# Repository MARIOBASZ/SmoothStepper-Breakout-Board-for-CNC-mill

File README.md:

# SmoothStepper Breakout Board for CNC-mill

A KiCAd project for a single sided PCB with isolated I/0, 10A relay for spindle.
For fully isolated I/O including motor control use stepper drivers such as DM420A or DQ542MA.

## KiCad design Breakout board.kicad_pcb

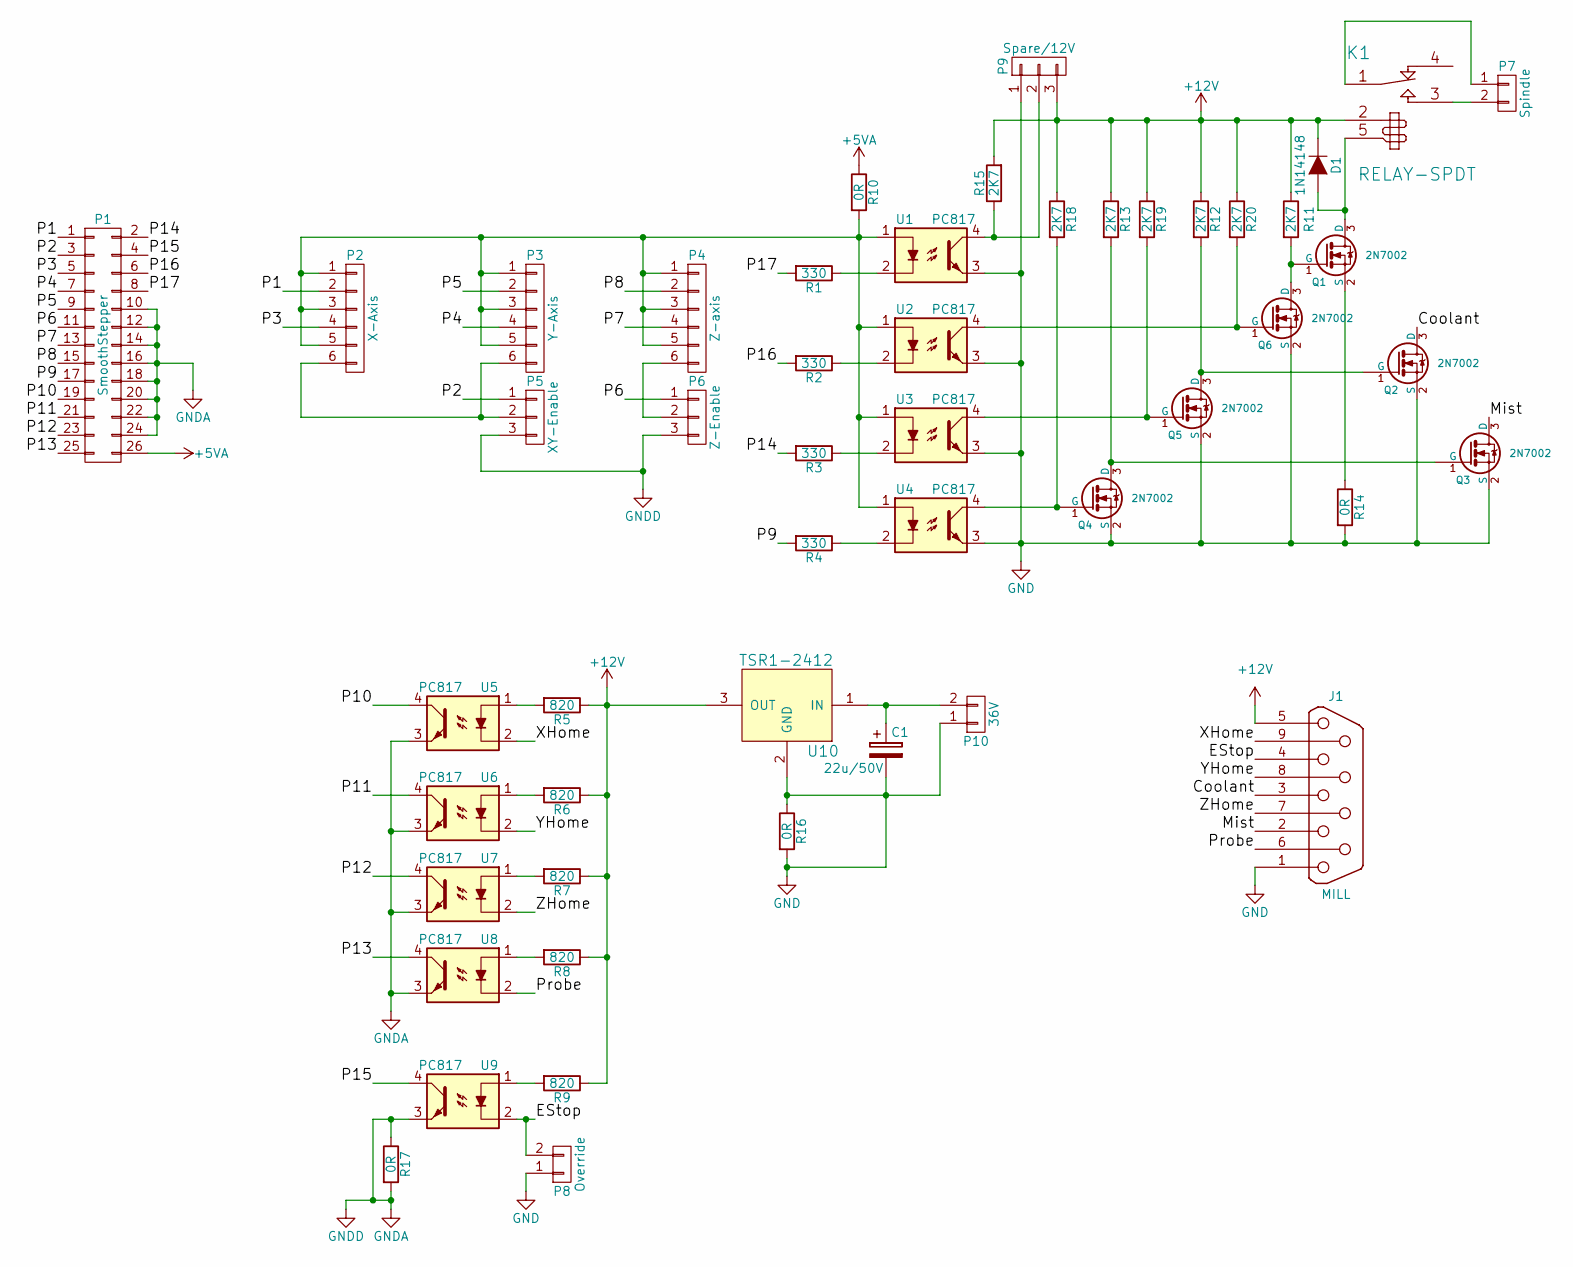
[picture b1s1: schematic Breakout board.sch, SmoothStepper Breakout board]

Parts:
C1: 22u/50V; CP_Tantalum_Case-D_EIA-7343-31_Reflow
D1: 1N14148; D_SOD-123
J1: MILL; DB9_8LCM009S
K1: RELAY-SPDT; Relay_SANYOU_SRD_Series_Form_C
P1: SmoothStepper; IDC_Header_Straight_26pins
P2: X-Axis; CONN_PWR_6P_3.5MM
P3: Y-Axis; CONN_PWR_6P_3.5MM
P4: Z-axis; CONN_PWR_6P_3.5MM
P5: XY-Enable; Pin_Header_Straight_1x03_Pitch2.54mm
P6: Z-Enable; Pin_Header_Straight_1x03_Pitch2.54mm
P7: Spindle; TerminalBlock_Pheonix_MKDS1.5-2pol
P8: Override; Pin_Header_Straight_1x02_Pitch2.54mm
P9: Spare/12V; Pin_Header_Straight_1x03_Pitch2.54mm
P10: 36V; TerminalBlock_Pheonix_MKDS1.5-2pol
Q1, Q2, Q3, Q4, Q5, Q6: 2N7002; SOT-23
R1, R2, R3, R4: 330; R_1206
R5, R6, R7, R8, R9: 820; R_1206
R10, R14, R16, R17: 0R; R_1206
R11, R12, R13, R15, R18, R19, R20: 2K7; R_1206
U1, U2, U3, U4, U5, U6, U7, U8, U9: PC817; OPTOCOUPLER_W00
U10: TSR1-2412; TSR_1

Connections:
+5VA: P1.26, R10.1
/Coolant: J1.3, Q2.3 (D)
/EStop: J1.4, P8.2, U9.2
/Mist: J1.2, Q3.3 (D)
/P1: P1.1, P2.2
/P2: P1.3, P5.1
/P3: P1.5, P2.4
/P4: P1.7, P3.4
/P5: P1.9, P3.2
/P6: P1.11, P6.1
/P7: P1.13, P4.4
/P8: P1.15, P4.2
/P9: P1.17, R4.2
/P10: P1.19, U5.4
/P11: P1.21, U6.4
/P12: P1.23, U7.4
/P13: P1.25, U8.4
/P14: P1.2, R3.2
/P15: P1.4, U9.4
/P16: P1.6, R2.2
/P17: P1.8, R1.2
/Probe: J1.6, U8.2
/XHome: J1.9, U5.2
/YHome: J1.8, U6.2
/ZHome: J1.7, U7.2
GND: C1.2, J1.1, P8.1, P9.1, P10.1, Q2.2 (S), Q3.2 (S), Q4.2 (S), Q5.2 (S), Q6.2 (S), R14.2, R16.1, R16.2, U1.3, U2.3, U3.3, U4.3, U10.2 (GND)
GNDA: P1.10, P1.12, P1.14, P1.16, P1.18, P1.20, P1.22, P1.24, P5.3, P6.3, R17.1, R17.2, U5.3, U6.3, U7.3, U8.3, U9.3
unnamed: C1.1, P10.2, U10.1 (IN)
unnamed: D1.2 (A), K1.5, Q1.3 (D)
unnamed: K1.1 (COM), P7.1
unnamed: K1.3 (NO), P7.2
unnamed: P2.1, P2.3, P2.5, P3.1, P3.3, P3.5, P4.1, P4.3, P4.5, R10.2, U1.1, U2.1, U3.1, U4.1
unnamed: P2.6, P3.6, P5.2
unnamed: P4.6, P6.2
unnamed: Q1.1 (G), Q6.3 (D), R11.2
unnamed: Q1.2 (S), R14.1
unnamed: Q2.1 (G), Q5.3 (D), R12.2
unnamed: Q3.1 (G), Q4.3 (D), R13.2
unnamed: Q4.1 (G), R18.2, U4.4
unnamed: Q5.1 (G), R19.2, U3.4
unnamed: Q6.1 (G), R20.2, U2.4
unnamed: R1.1, U1.2
unnamed: R2.1, U2.2
unnamed: R3.1, U3.2
unnamed: R4.1, U4.2
unnamed: R5.2, U5.1
unnamed: R6.2, U6.1
unnamed: R7.2, U7.1
unnamed: R8.2, U8.1
unnamed: R9.2, U9.1

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
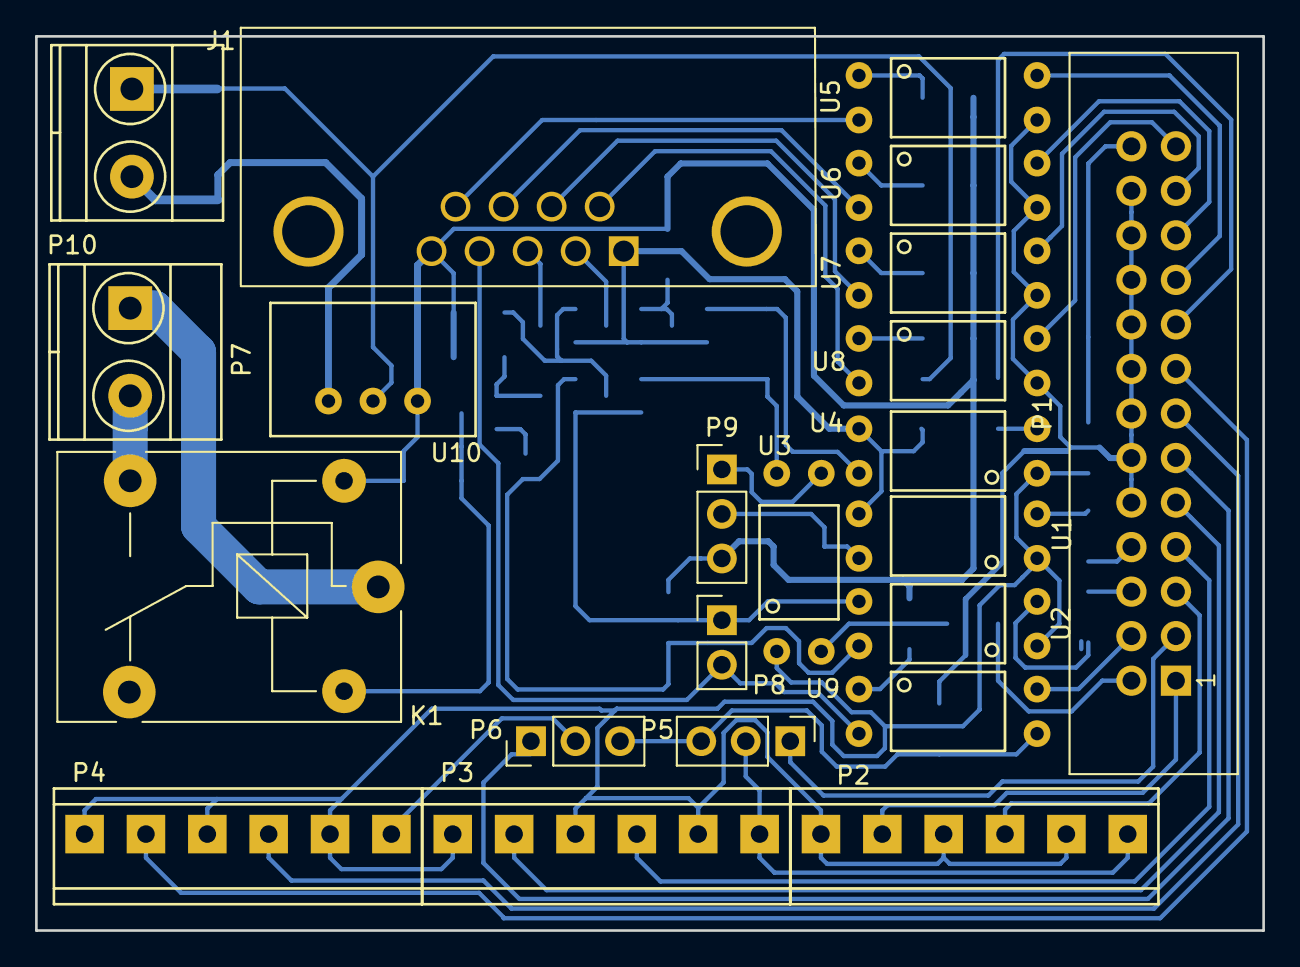
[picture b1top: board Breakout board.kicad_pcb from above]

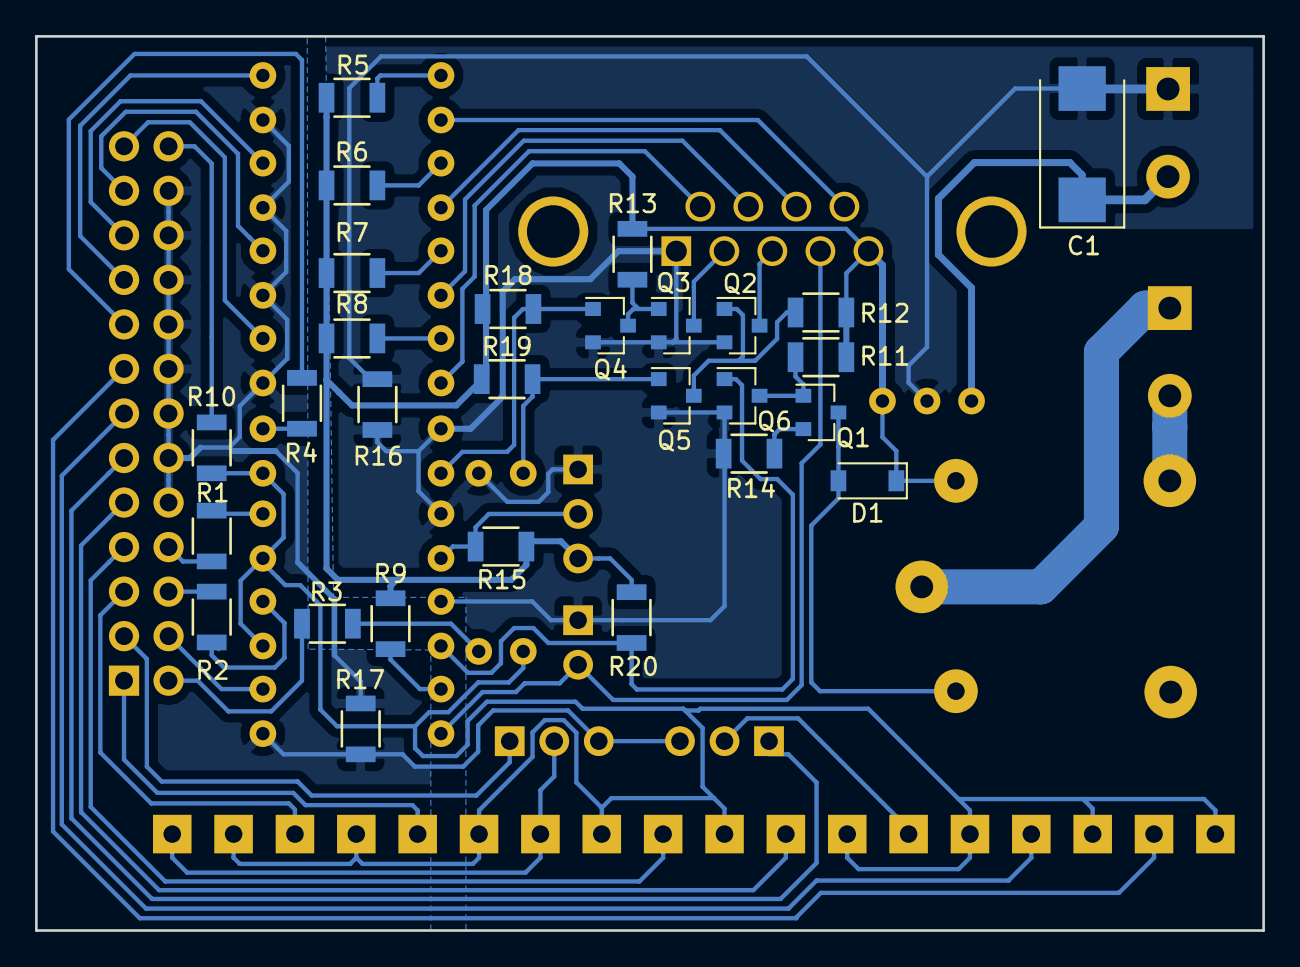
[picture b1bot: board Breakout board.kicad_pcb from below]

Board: 2 copper layers, 70.0 x 51.0 mm, 50 parts (28 on the bottom side), 52 nets.

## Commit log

2017-05-21 :neckbeard: Added .gitattributes & .gitignore files
2017-10-17 Added PCB image

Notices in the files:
Breakout board.kicad_pcb:
Licensed under CERN OHL v.1.2 or later
